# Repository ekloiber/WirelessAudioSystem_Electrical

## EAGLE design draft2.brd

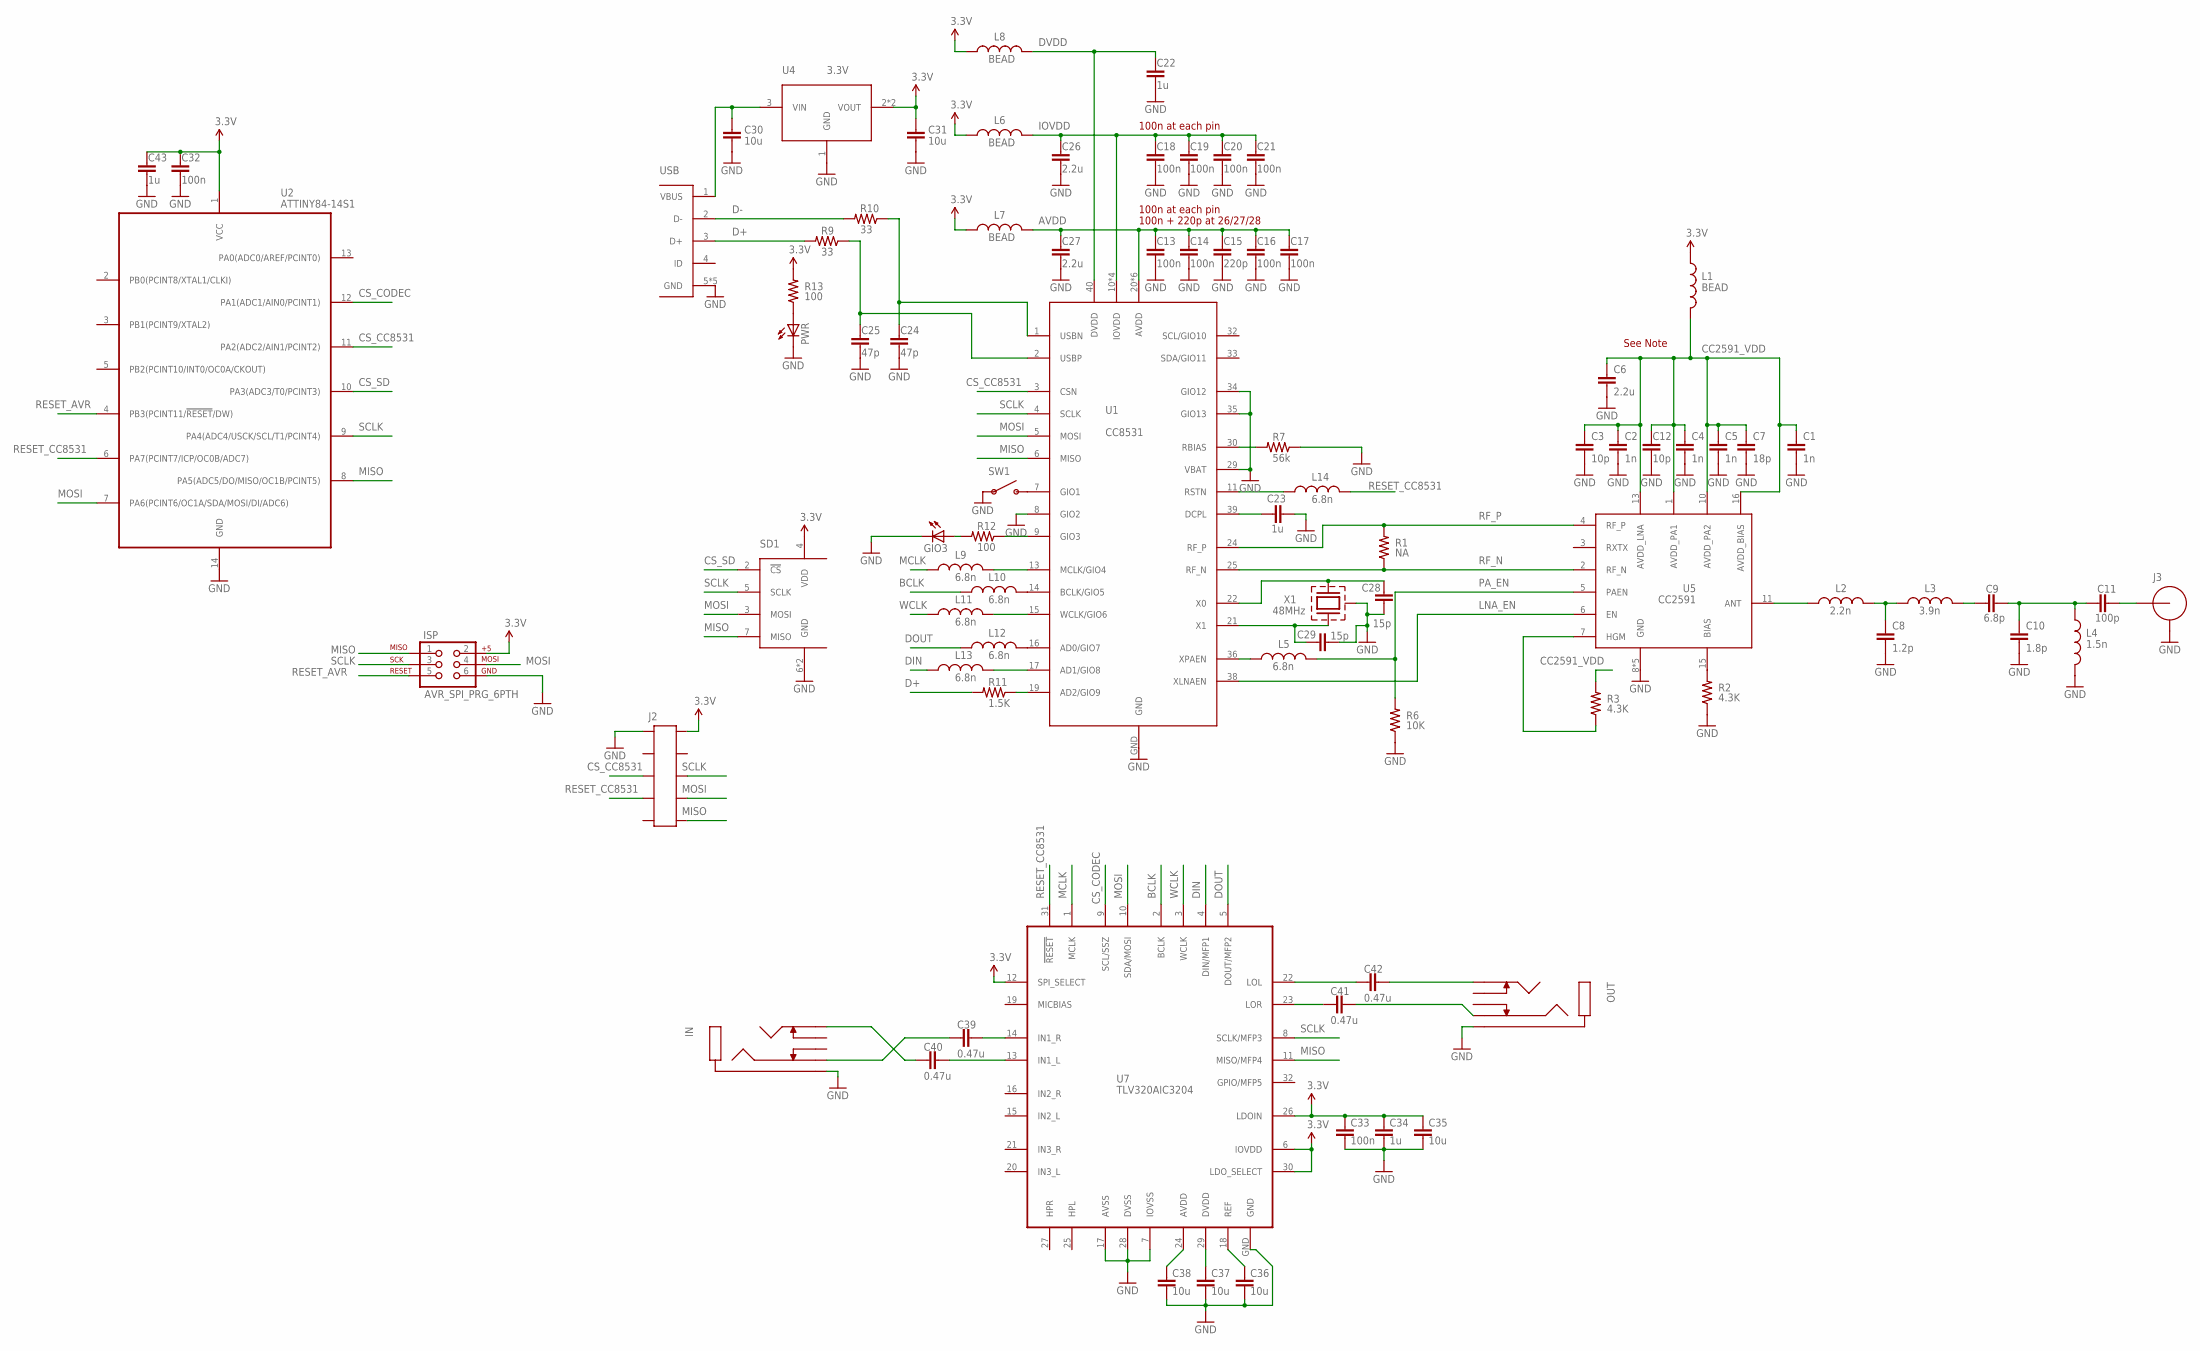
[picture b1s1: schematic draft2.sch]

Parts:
C1, C2, C4, C5: 1n; C0603
C3, C12: 10p; C0603
C6, C26, C27: 2.2u; C0603
C7: 18p; C0603
C8: 1.2p; C0603
C9: 6.8p; C0603
C10: 1.8p; C0603
C11: 100p; C0603
C13, C14, C16, C17, C18, C19, C20, C21, C32, C33: 100n; C0603
C15: 220p; C0603
C22, C23, C34, C43: 1u; C0603
C24, C25: 47p; C0603
C28, C29: 15p; C0603
C30, C31, C35, C36, C37, C38: 10u; C0603
C39, C40, C41, C42: 0.47u; C0603
GIO3: LEDCHIP-LED0603; CHIP-LED0603
IN: PHONE_SW; 35RAPC4BV4
ISP: AVR_SPI_PRG_6PTH; 2X3
J2: HEADER-10P-SMD-MALE; 10P-0.05-HEADER
J3: SMA; CONSMA003.031
L1, L6, L7, L8: BEAD; 0603
L2: 2.2n; 0603
L3: 3.9n; 0603
L4: 1.5n; 0603
L5, L9, L10, L11, L12, L13, L14: 6.8n; 0603
OUT: PHONE_SW; 35RAPC4BV4
PWR: LEDCHIP-LED0603; CHIP-LED0603
R1: NA; R0603
R2, R3: 4.3K; R0603
R6: 10K; R0603
R7: 56k; R0603
R9, R10: 33; R0603
R11: 1.5K; R0603
R12, R13: 100; R0603
SD1: MICROSDDM3AT; DM3AT
SW1: SPST-SMD; TACT_SW
U1: CC8531; S-PVQFN-N40
U2: ATTINY84-14S1; SOIC14
U4: 3.3V; SOT-223
U5: CC2591; S-PVQFN-N16
U7: TLV320AIC3204; S-PVQFN-N32
USB: USB_MICRO_AB
X1: 48MHz; ABM3C

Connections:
3.3V: C31.1, C32.1, C33.1, C34.1, C35.1, C43.1, ISP.2, J2.2, L1.1, L6.1, L7.1, L8.1, R13.2, SD1.4 (VDD), U2.1 (VCC), U4.2 (VOUT), U4.4 (VOUT), U7.6 (IOVDD), U7.12 (SPI_SELECT), U7.26 (LDOIN), U7.30 (LDO_SELECT)
AVDD: C13.1, C14.1, C15.1, C16.1, C17.1, C27.1, L7.2, U1.20 (AVDD), U1.23 (AVDD), U1.26 (AVDD), U1.27 (AVDD), U1.28 (AVDD), U1.31 (AVDD)
BCLK: L10.1, U7.2 (BCLK)
CC2591_VDD: C1.1, C2.1, C3.1, C4.1, C5.1, C6.1, C7.1, C12.1, L1.2, R3.2, U5.1 (AVDD_PA1), U5.10 (AVDD_PA2), U5.13 (AVDD_LNA), U5.16 (AVDD_BIAS)
CS_CC8531: J2.5, U1.3 (CSN), U2.11 (PA2(ADC2/AIN1/PCINT2))
CS_CODEC: U2.12 (PA1(ADC1/AIN0/PCINT1)), U7.9 (SCL/SSZ)
CS_SD: SD1.2 (!CS), U2.10 (PA3(ADC3/T0/PCINT3))
D+: R9.2, R11.2, USB.3 (D+)
D-: R10.2, USB.2 (D-)
DIN: L13.1, U7.4 (DIN/MFP1)
DOUT: L12.1, U7.5 (DOUT/MFP2)
DVDD: C22.1, L8.2, U1.40 (DVDD)
GND: C1.2, C2.2, C3.2, C4.2, C5.2, C6.2, C7.2, C8.2, C10.2, C12.2, C13.2, C14.2, C15.2, C16.2, C17.2, C18.2, C19.2, C20.2, C21.2, C22.2, C23.2, C24.2, C25.2, C26.2, C27.2, C28.2, C29.2, C30.2, C31.2, C32.2, C33.2, C34.2, C35.2, C36.2, C37.2, C38.2, C43.2, GIO3.C, IN.1 (GND), ISP.6, J2.1, J3.GND1 (GND), J3.GND2 (GND), J3.GND3 (GND), J3.GND4 (GND), L4.2, OUT.1 (GND), PWR.C, R2.1, R6.1, R7.1, SD1.6 (GND), SD1.GND, SW1.1, SW1.2, U1.8 (GIO2), U1.29 (VBAT), U1.34 (GIO12), U1.35 (GIO13), U1.GND, U2.14 (GND), U4.1 (GND), U5.8 (GND), U5.9 (GND), U5.12 (GND), U5.14 (GND), U5.GND, U7.7 (IOVSS), U7.17 (AVSS), U7.28 (DVSS), U7.GND, USB.5 (GND), USB.GND1 (GND), USB.GND2 (GND), USB.GND3 (GND), USB.GND4 (GND), X1.2 (CASE), X1.4 (CASE)
IOVDD: C18.1, C19.1, C20.1, C21.1, C26.1, L6.2, U1.10 (IOVDD), U1.12 (IOVDD), U1.18 (IOVDD), U1.37 (IOVDD)
IOVDD1: C24.1, R10.1, U1.1 (USBN)
IOVDD2: C25.1, R9.1, U1.2 (USBP)
LNA_EN: U1.38 (XLNAEN), U5.6 (EN)
MCLK: L9.1, U7.1 (MCLK)
MISO: ISP.1, J2.10, SD1.7 (MISO), U1.6 (MISO), U2.8 (PA5(ADC5/DO/MISO/OC1B/PCINT5)), U7.11 (MISO/MFP4)
MOSI: ISP.4, J2.8, SD1.3 (MOSI), U1.5 (MOSI), U2.7 (PA6(PCINT6/OC1A/SDA/MOSI/DI/ADC6)), U7.10 (SDA/MOSI)
unnamed: C29.1, U1.21 (X1), X1.1
unnamed: C28.1, U1.22 (X0), X1.3 (2)
unnamed: L14.1, U1.11 (RSTN)
unnamed: C30.1, U4.3 (VIN), USB.1 (VBUS)
unnamed: R2.2, U5.15 (BIAS)
unnamed: R3.1, U5.7 (HGM)
unnamed: C11.2, J3.SIG
unnamed: C38.1, U7.24 (AVDD)
unnamed: L2.1, U5.11 (ANT)
unnamed: C8.1, L2.2, L3.1
unnamed: C9.1, L3.2
unnamed: C9.2, C10.1, C11.1, L4.1
unnamed: L5.1, U1.36 (XPAEN)
unnamed: R7.2, U1.30 (RBIAS)
unnamed: C36.1, U7.18 (REF)
unnamed: C23.1, U1.39 (DCPL)
unnamed: L10.2, U1.14 (BCLK/GIO5)
unnamed: L9.2, U1.13 (MCLK/GIO4)
unnamed: R11.1, U1.19 (AD2/GIO9)
unnamed: L11.2, U1.15 (WCLK/GIO6)
unnamed: L12.2, U1.16 (AD0/GIO7)
unnamed: L13.2, U1.17 (AD1/GIO8)
unnamed: R12.1, U1.9 (GIO3)
unnamed: GIO3.A, R12.2
unnamed: SW1.3, SW1.4, U1.7 (GIO1)
unnamed: PWR.A, R13.1
unnamed: C37.1, U7.29 (DVDD)
unnamed: C40.1, IN.2 (L)
unnamed: C39.2, U7.14 (IN1_R)
unnamed: C40.2, U7.13 (IN1_L)
unnamed: C39.1, IN.4 (R)
unnamed: C42.2, OUT.2 (L)
unnamed: C41.2, OUT.4 (R)
unnamed: C42.1, U7.22 (LOL)
unnamed: C41.1, U7.23 (LOR)
PA_EN: L5.2, R6.2, U5.5 (PAEN)
RESET_AVR: ISP.5, U2.4 (PB3(PCINT11/!RESET!/DW))
RESET_CC8531: J2.7, L14.2, U2.6 (PA7(PCINT7/ICP/OC0B/ADC7)), U7.31 (!RESET)
RF_N: R1.1, U1.25 (RF_N), U5.2 (RF_N)
RF_P: R1.2, U1.24 (RF_P), U5.4 (RF_P)
SCLK: ISP.3, J2.6, SD1.5 (SCLK), U1.4 (SCLK), U2.9 (PA4(ADC4/USCK/SCL/T1/PCINT4)), U7.8 (SCLK/MFP3)
WCLK: L11.1, U7.3 (WCLK)

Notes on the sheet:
See Note
100n at each pin
100n + 220p at 26/27/28

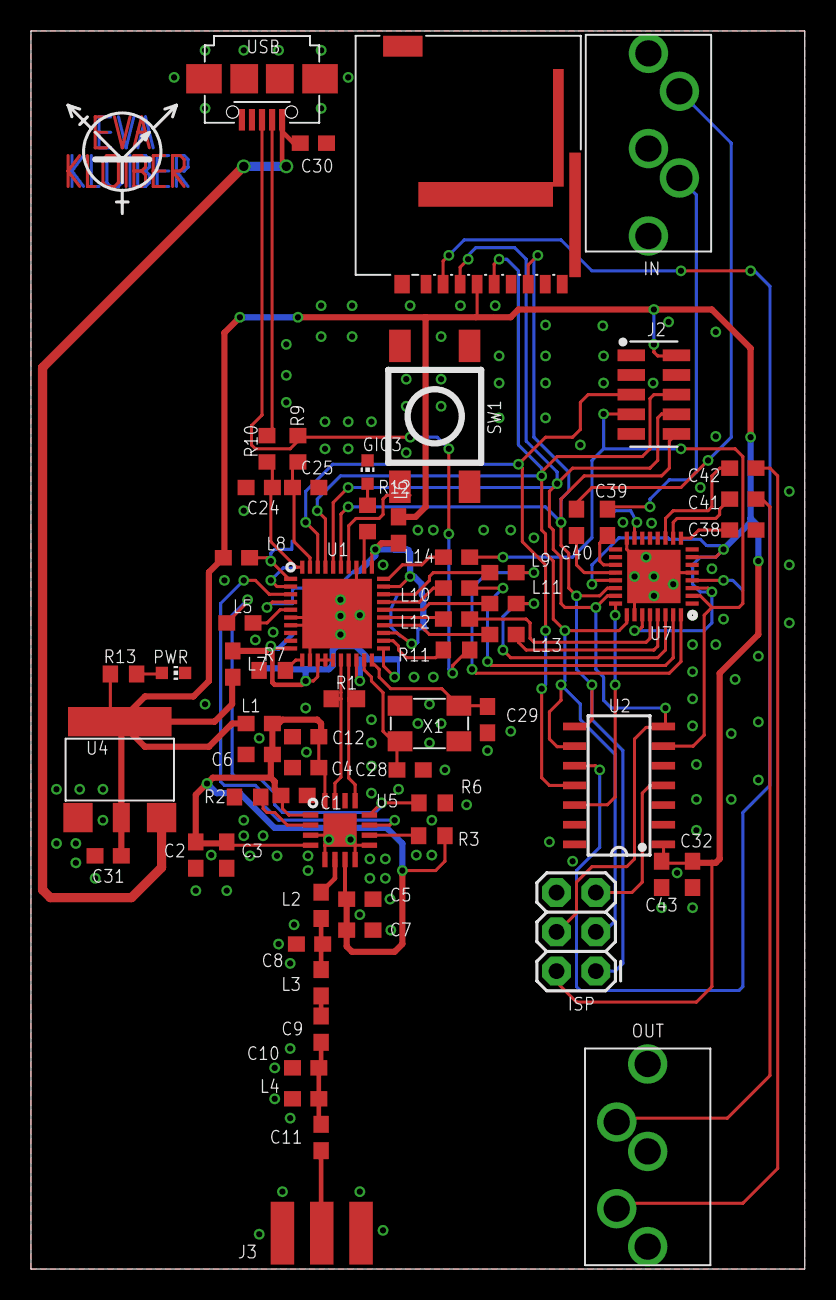
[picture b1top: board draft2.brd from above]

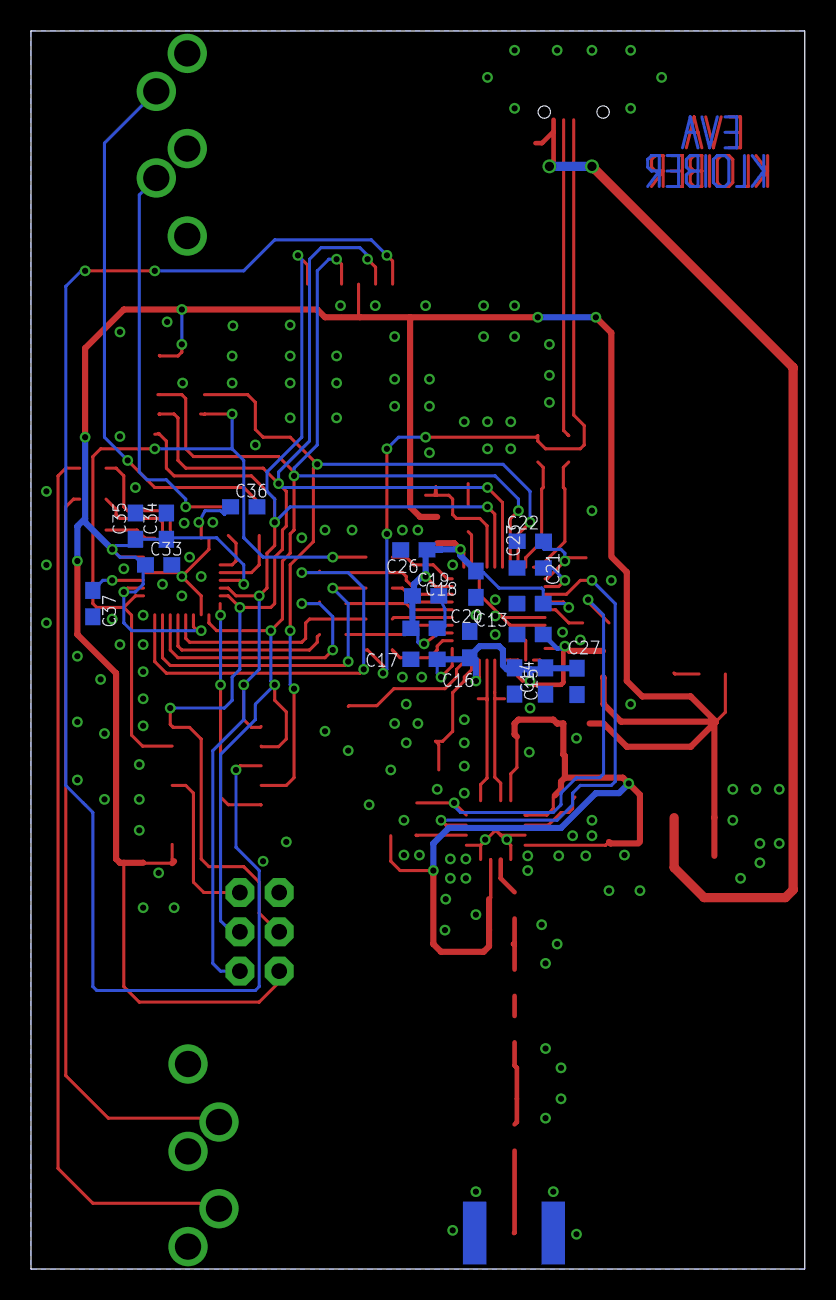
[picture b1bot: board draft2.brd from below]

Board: 2 copper layers, 50.0 x 80.0 mm, 84 parts (18 on the bottom side), 62 nets.

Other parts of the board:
U$1: TRANS

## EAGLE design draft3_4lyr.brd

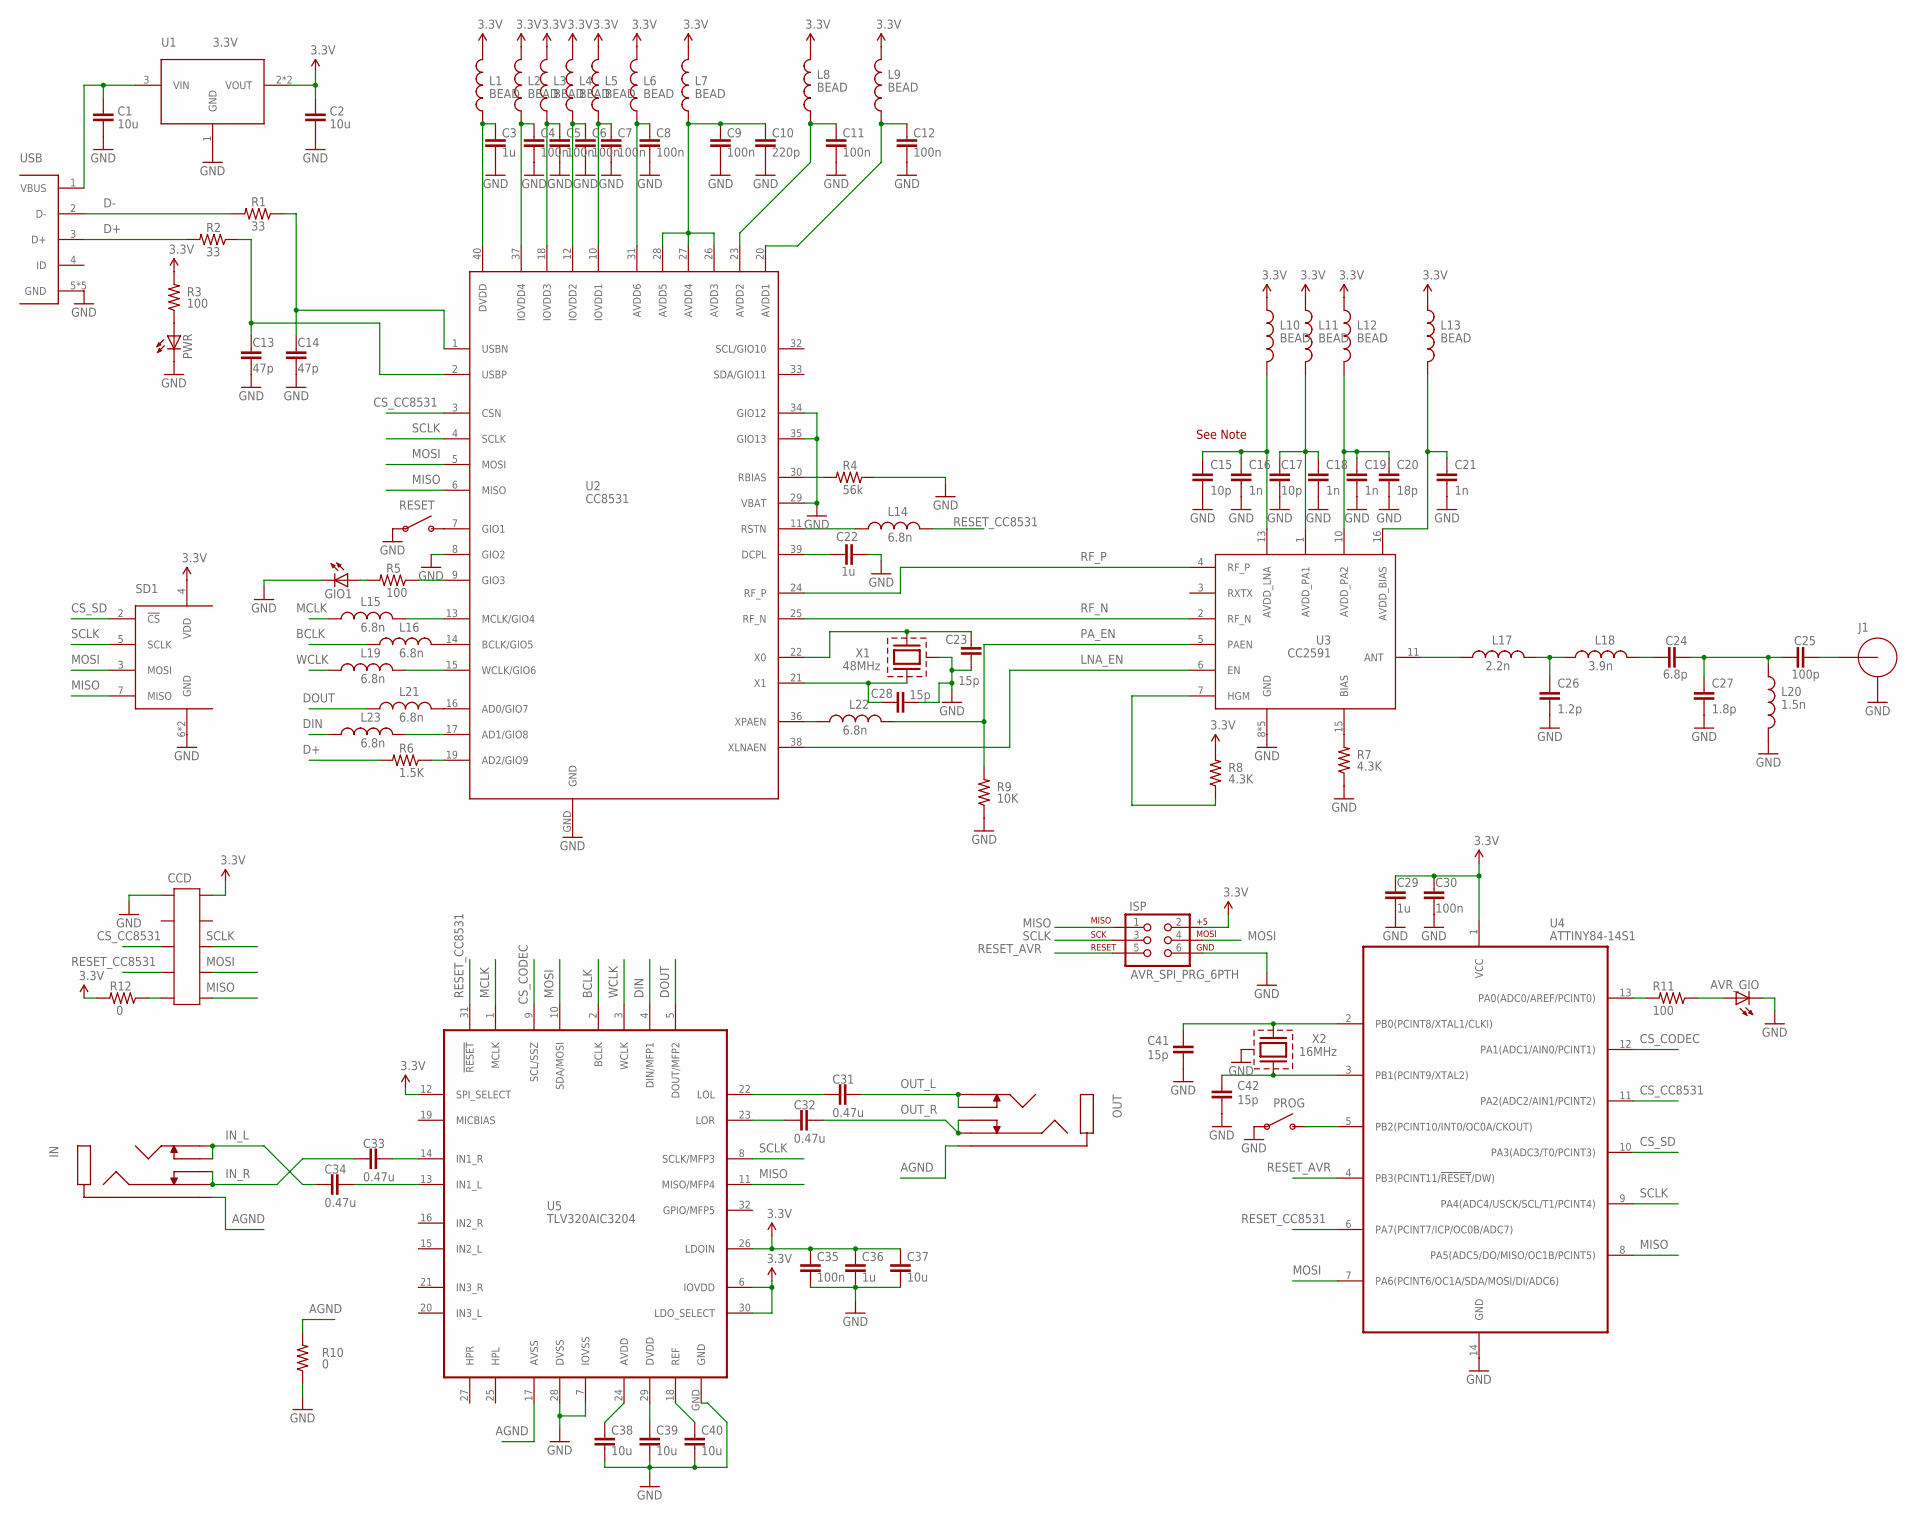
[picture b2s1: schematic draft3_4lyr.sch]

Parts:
AVR_GIO: LEDCHIP-LED0603; CHIP-LED0603
C1, C2, C37, C38, C39, C40: 10u; C0603
C3, C22, C29, C36: 1u; C0603
C4, C5, C6, C7, C8, C9, C11, C12, C30, C35: 100n; C0603
C10: 220p; C0603
C13, C14: 47p; C0603
C15, C17: 10p; C0603
C16, C18, C19, C21: 1n; C0603
C20: 18p; C0603
C23, C28, C41, C42: 15p; C0603
C24: 6.8p; C0603
C25: 100p; C0603
C26: 1.2p; C0603
C27: 1.8p; C0603
C31, C32, C33, C34: 0.47u; C0603
CCD: HEADER-10P-PTH-MALE; 2X5
GIO1: LEDCHIP-LED0603; CHIP-LED0603
IN: PHONE_SW; 35RAPC4BV4
ISP: AVR_SPI_PRG_6PTH; 2X3
J1: SMA; CONSMA003.031
L1, L2, L3, L4, L5, L6, L7, L8, L9, L10, L11, L12, L13: BEAD; 0603
L14, L15, L16, L19, L21, L22, L23: 6.8n; 0603
L17: 2.2n; 0603
L18: 3.9n; 0603
L20: 1.5n; 0603
OUT: PHONE_SW; 35RAPC4BV4
PROG: SPST-SMD; TACT_SW
PWR: LEDCHIP-LED0603; CHIP-LED0603
R1, R2: 33; R0603
R3, R5, R11: 100; R0603
R4: 56k; R0603
R6: 1.5K; R0603
R7, R8: 4.3K; R0603
R9: 10K; R0603
R10, R12: 0; R0603
RESET: SPST-SMD; TACT_SW
SD1: MICROSDDM3AT; DM3AT
U1: 3.3V; SOT-223
U2: CC8531; S-PVQFN-N40
U3: CC2591; S-PVQFN-N16
U4: ATTINY84-14S1; SOIC14
U5: TLV320AIC3204; S-PVQFN-N32
USB: USB_MICRO_AB
X1: 48MHz; ABM3C
X2: 16MHz; ABMM

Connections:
3.3V: C2.1, C29.1, C30.1, C35.1, C36.1, C37.1, CCD.2, ISP.2, L1.2, L2.2, L3.2, L4.2, L5.2, L6.2, L7.2, L8.2, L9.2, L10.1, L11.1, L12.1, L13.1, R3.2, R8.2, R12.2, SD1.4 (VDD), U1.2 (VOUT), U1.4 (VOUT), U4.1 (VCC), U5.6 (IOVDD), U5.12 (SPI_SELECT), U5.26 (LDOIN), U5.30 (LDO_SELECT)
AGND: IN.1 (GND), OUT.1 (GND), R10.2, U5.17 (AVSS)
AVDD: C38.1, U5.24 (AVDD)
AVDD_BIAS: C21.1, L13.2, U3.16 (AVDD_BIAS)
AVDD_LNA: C15.1, C16.1, L10.2, U3.13 (AVDD_LNA)
AVDD_PA1: C17.1, C18.1, L11.2, U3.1 (AVDD_PA1)
AVDD_PA2: C19.1, C20.1, L12.2, U3.10 (AVDD_PA2)
BCLK: L16.1, U5.2 (BCLK)
CS_CC8531: CCD.5, U2.3 (CSN), U4.11 (PA2(ADC2/AIN1/PCINT2))
CS_CODEC: U4.12 (PA1(ADC1/AIN0/PCINT1)), U5.9 (SCL/SSZ)
CS_SD: SD1.2 (!CS), U4.10 (PA3(ADC3/T0/PCINT3))
D+: R2.2, R6.2, USB.3 (D+)
D-: R1.2, USB.2 (D-)
DIN: L23.1, U5.4 (DIN/MFP1)
DOUT: L21.1, U5.5 (DOUT/MFP2)
DVDD: C39.1, U5.29 (DVDD)
GND: AVR_GIO.C, C1.2, C2.2, C3.2, C4.2, C5.2, C6.2, C7.2, C8.2, C9.2, C10.2, C11.2, C12.2, C13.2, C14.2, C15.2, C16.2, C17.2, C18.2, C19.2, C20.2, C21.2, C22.2, C23.2, C26.2, C27.2, C28.2, C29.2, C30.2, C35.2, C36.2, C37.2, C38.2, C39.2, C40.2, C41.1, C42.1, CCD.1, GIO1.C, ISP.6, J1.GND1 (GND), J1.GND2 (GND), J1.GND3 (GND), J1.GND4 (GND), L20.2, PROG.1, PROG.2, PWR.C, R4.1, R7.1, R9.1, R10.1, RESET.1, RESET.2, SD1.6 (GND), SD1.GND, U1.1 (GND), U2.8 (GIO2), U2.29 (VBAT), U2.34 (GIO12), U2.35 (GIO13), U2.GND, U3.8 (GND), U3.9 (GND), U3.12 (GND), U3.14 (GND), U3.GND, U4.14 (GND), U5.7 (IOVSS), U5.28 (DVSS), U5.GND, USB.5 (GND), USB.GND1 (GND), USB.GND2 (GND), USB.GND3 (GND), USB.GND4 (GND), X1.2 (CASE), X1.4 (CASE), X2.2 (CASE), X2.4 (CASE)
IN_L: C34.1, IN.2 (L), IN.5 (L_SW)
IN_R: C33.1, IN.3 (R_SW), IN.4 (R)
IOVDD1: C14.1, R1.1, U2.1 (USBN)
IOVDD2: C13.1, R2.1, U2.2 (USBP)
LNA_EN: U2.38 (XLNAEN), U3.6 (EN)
MCLK: L15.1, U5.1 (MCLK)
MISO: CCD.10, ISP.1, SD1.7 (MISO), U2.6 (MISO), U4.8 (PA5(ADC5/DO/MISO/OC1B/PCINT5)), U5.11 (MISO/MFP4)
MOSI: CCD.8, ISP.4, SD1.3 (MOSI), U2.5 (MOSI), U4.7 (PA6(PCINT6/OC1A/SDA/MOSI/DI/ADC6)), U5.10 (SDA/MOSI)
unnamed: C28.1, U2.21 (X1), X1.1
unnamed: C23.1, U2.22 (X0), X1.3 (2)
unnamed: L14.1, U2.11 (RSTN)
unnamed: PROG.3, PROG.4, U4.5 (PB2(PCINT10/INT0/OC0A/CKOUT))
unnamed: L16.2, U2.14 (BCLK/GIO5)
unnamed: C1.1, U1.3 (VIN), USB.1 (VBUS)
unnamed: R7.2, U3.15 (BIAS)
unnamed: R8.1, U3.7 (HGM)
unnamed: C25.2, J1.SIG
unnamed: L21.2, U2.16 (AD0/GIO7)
unnamed: RESET.3, RESET.4, U2.7 (GIO1)
unnamed: L17.1, U3.11 (ANT)
unnamed: C26.1, L17.2, L18.1
unnamed: C24.1, L18.2
unnamed: C24.2, C25.1, C27.1, L20.1
unnamed: C9.1, C10.1, L7.1, U2.26 (AVDD3), U2.27 (AVDD4), U2.28 (AVDD5)
unnamed: L22.1, U2.36 (XPAEN)
unnamed: R4.2, U2.30 (RBIAS)
unnamed: C22.1, U2.39 (DCPL)
unnamed: C11.1, L8.1, U2.23 (AVDD2)
unnamed: L15.2, U2.13 (MCLK/GIO4)
unnamed: R6.1, U2.19 (AD2/GIO9)
unnamed: L19.2, U2.15 (WCLK/GIO6)
unnamed: C12.1, L9.1, U2.20 (AVDD1)
unnamed: L23.2, U2.17 (AD1/GIO8)
unnamed: R5.1, U2.9 (GIO3)
unnamed: GIO1.A, R5.2
unnamed: C8.1, L6.1, U2.31 (AVDD6)
unnamed: PWR.A, R3.1
unnamed: C33.2, U5.14 (IN1_R)
unnamed: C34.2, U5.13 (IN1_L)
unnamed: C31.1, U5.22 (LOL)
unnamed: C32.1, U5.23 (LOR)
unnamed: C7.1, L5.1, U2.10 (IOVDD1)
unnamed: C6.1, L4.1, U2.12 (IOVDD2)
unnamed: C5.1, L3.1, U2.18 (IOVDD3)
unnamed: C4.1, L2.1, U2.37 (IOVDD4)
unnamed: C3.1, L1.1, U2.40 (DVDD)
unnamed: R11.2, U4.13 (PA0(ADC0/AREF/PCINT0))
unnamed: AVR_GIO.A, R11.1
unnamed: C41.2, U4.2 (PB0(PCINT8/XTAL1/CLKI)), X2.1
unnamed: C42.2, U4.3 (PB1(PCINT9/XTAL2)), X2.3 (2)
unnamed: CCD.9, R12.1
OUT_L: C31.2, OUT.2 (L), OUT.5 (L_SW)
OUT_R: C32.2, OUT.3 (R_SW), OUT.4 (R)
PA_EN: L22.2, R9.2, U3.5 (PAEN)
REF: C40.1, U5.18 (REF)
RESET_AVR: ISP.5, U4.4 (PB3(PCINT11/!RESET!/DW))
RESET_CC8531: CCD.7, L14.2, U4.6 (PA7(PCINT7/ICP/OC0B/ADC7)), U5.31 (!RESET)
RF_N: U2.25 (RF_N), U3.2 (RF_N)
RF_P: U2.24 (RF_P), U3.4 (RF_P)
SCLK: CCD.6, ISP.3, SD1.5 (SCLK), U2.4 (SCLK), U4.9 (PA4(ADC4/USCK/SCL/T1/PCINT4)), U5.8 (SCLK/MFP3)
WCLK: L19.1, U5.3 (WCLK)

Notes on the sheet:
See Note

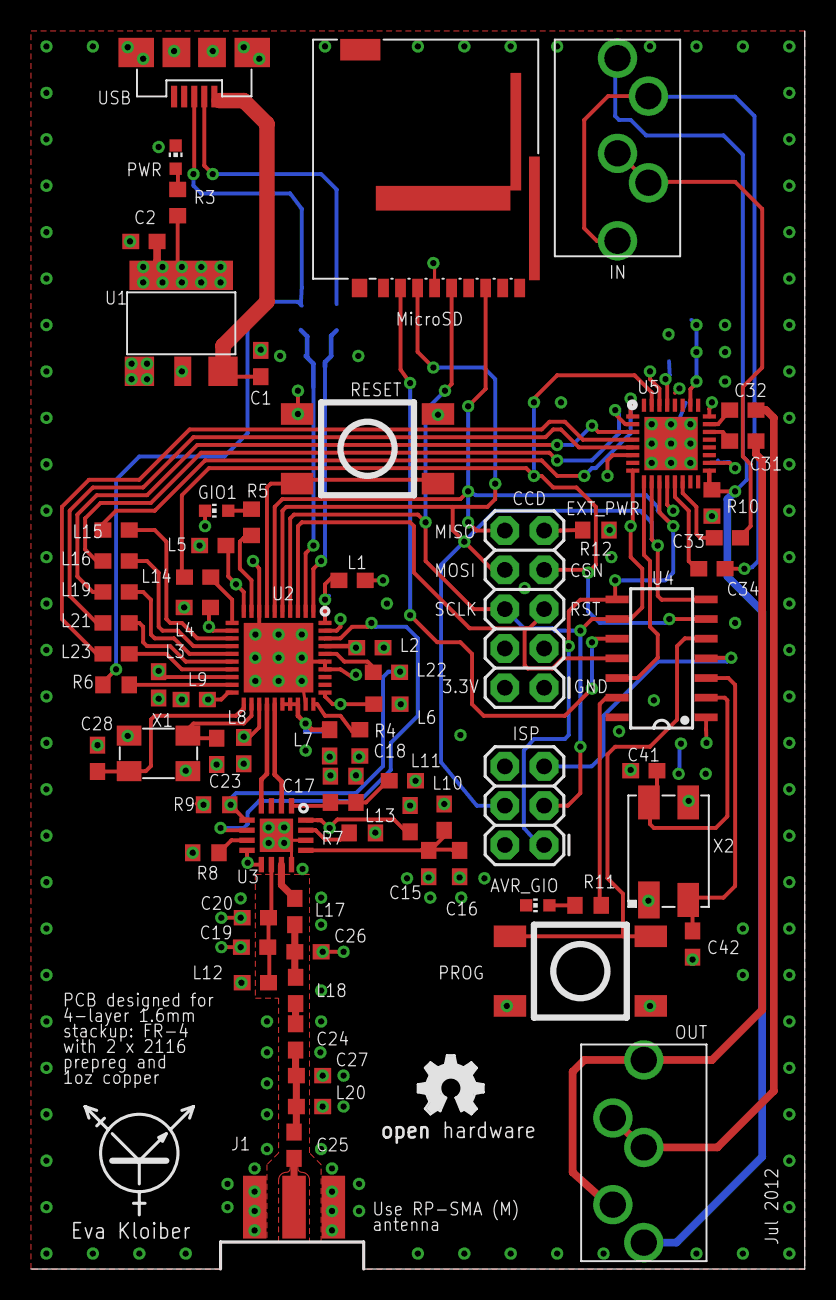
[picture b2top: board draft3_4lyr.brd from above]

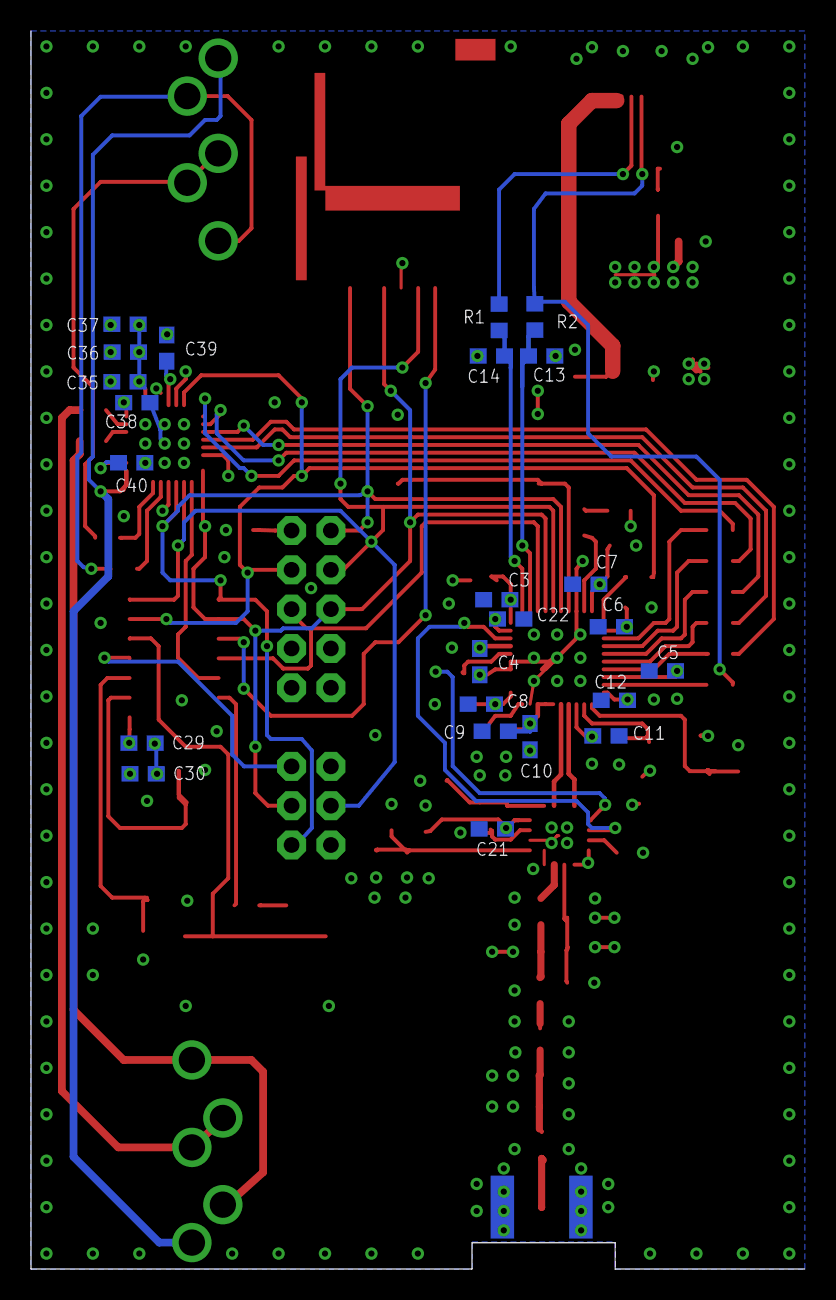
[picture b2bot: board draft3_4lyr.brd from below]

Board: 4 copper layers, 50.0 x 80.0 mm, 99 parts (24 on the bottom side), 78 nets.

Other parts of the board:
U$1: HAMMOND_1455C802
U$4: TRANS_SILK
U$5: OSHW_FILLX150_NOTEXT

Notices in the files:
parts and their libraries:
SparkFun: Licensing: CC v3.0 Share-Alike You are welcome to use this library for commercial purposes.
